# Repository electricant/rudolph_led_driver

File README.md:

# rudolph_led_driver
Driver for LED fairy lights using Li-Ion batteries

## Board pictures

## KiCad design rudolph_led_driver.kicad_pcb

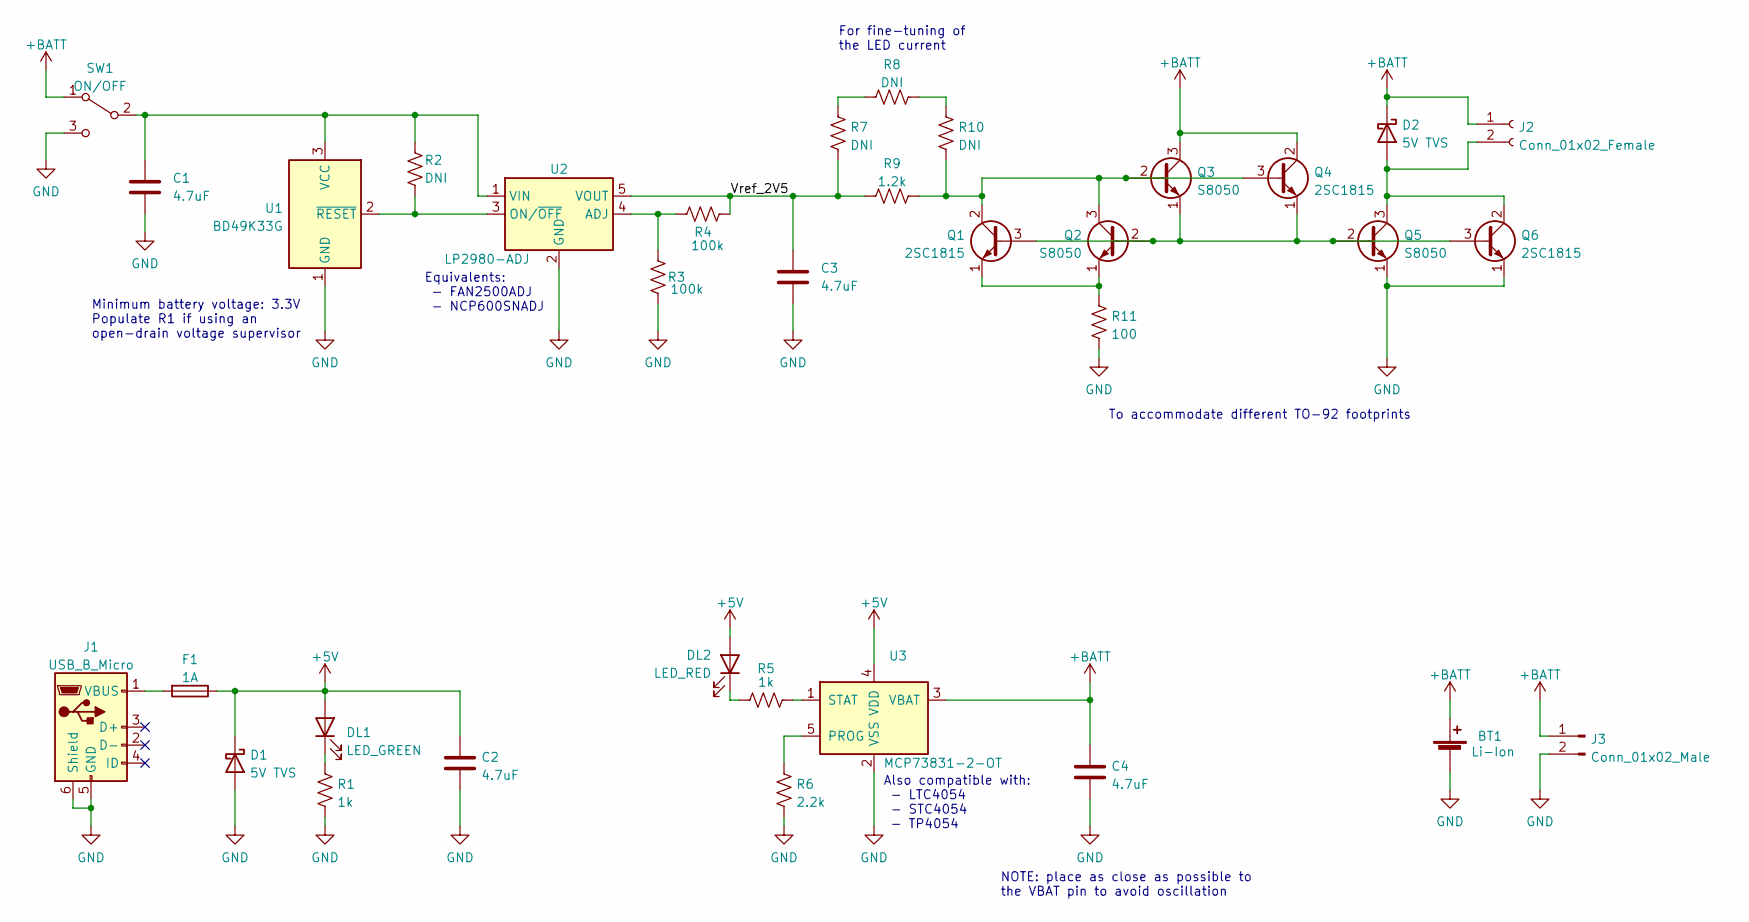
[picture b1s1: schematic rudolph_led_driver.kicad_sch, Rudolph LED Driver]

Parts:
BT1: Li-Ion; BatteryHolder_MPD_BH-18650-PC2
C1, C2, C3, C4: 4.7uF; C_0805_2012Metric_Pad1.18x1.45mm_HandSolder
D1, D2: 5V TVS; D_SOD-323_HandSoldering
DL1: LED_GREEN; D_0805_2012Metric_Pad1.15x1.40mm_HandSolder
DL2: LED_RED; D_0805_2012Metric_Pad1.15x1.40mm_HandSolder
F1: 1A; Fuse_0805_2012Metric_Pad1.15x1.40mm_HandSolder
J1: USB_B_Micro; USB_Micro-AB_Molex_47590-0001
J2: Conn_01x02_Female; PinSocket_1x02_P2.54mm_Vertical
J3: Conn_01x02_Male; PinHeader_1x02_P2.54mm_Vertical
Q1, Q4, Q6: 2SC1815; TO-92_Inline_Wide
Q2, Q3, Q5: S8050; TO-92_Inline_Wide
R1, R5: 1k; R_0805_2012Metric_Pad1.20x1.40mm_HandSolder
R2, R7, R8, R10: DNI; R_0805_2012Metric_Pad1.20x1.40mm_HandSolder
R3, R4: 100k; R_0805_2012Metric_Pad1.20x1.40mm_HandSolder
R6: 2.2k; R_0805_2012Metric_Pad1.20x1.40mm_HandSolder
R9: 1.2k; R_0805_2012Metric_Pad1.20x1.40mm_HandSolder
R11: 100; R_0805_2012Metric_Pad1.20x1.40mm_HandSolder
SW1: ON/OFF; PinHeader_1x03_P2.54mm_Vertical
U1: BD49K33G; SOT-23
U2: LP2980-ADJ; SOT-23-5
U3: MCP73831-2-OT; SOT-23-5

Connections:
+5V: C2.1, D1.1 (K), DL1.2 (A), DL2.2 (A), F1.1, U3.4 (VDD)
+BATT: BT1.1 (+), C4.1, D2.1 (K), J2.1, J3.1, Q3.3 (C), Q4.2 (C), SW1.1 (A), U3.3 (VBAT)
/Vref_2V5: C3.1, R4.2, R7.1, R9.1, U2.5 (VOUT)
GND: BT1.2 (-), C1.2, C2.2, C3.2, C4.2, D1.2 (A), J1.5 (GND), J1.6 (Shield), J3.2, Q5.1 (E), Q6.1 (E), R1.2, R3.2, R6.2, R11.2, SW1.3 (C), U1.1 (GND), U2.2 (GND), U3.2 (VSS)
unnamed: D2.2 (A), J2.2, Q5.3 (C), Q6.2 (C)
unnamed: DL1.1 (K), R1.1
unnamed: DL2.1 (K), R5.1
unnamed: F1.2, J1.1 (VBUS)
unnamed: Q1.3 (B), Q2.2 (B), Q3.1 (E), Q4.1 (E), Q5.2 (B), Q6.3 (B)
unnamed: Q1.2 (C), Q2.3 (C), Q3.2 (B), Q4.3 (B), R9.2, R10.1
unnamed: Q1.1 (E), Q2.1 (E), R11.1
unnamed: R7.2, R8.1
unnamed: R8.2, R10.2
unnamed: C1.1, R2.1, SW1.2 (B), U1.3 (VCC), U2.1 (VIN)
unnamed: R2.2, U1.2 (~RESET), U2.3 (ON/~OFF)
unnamed: R3.1, R4.1, U2.4 (ADJ)
unnamed: R6.1, U3.5 (PROG)
unnamed: R5.2, U3.1 (STAT)

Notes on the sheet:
Equivalents: - FAN2500ADJ - NCP600SNADJ
For fine-tuning of the LED current
Minimum battery voltage: 3.3V Populate R1 if using an open-drain voltage supervisor
NOTE: place as close as possible to the VBAT pin to avoid oscillation
Also compatible with: - LTC4054 - STC4054 - TP4054
To accommodate different TO-92 footprints

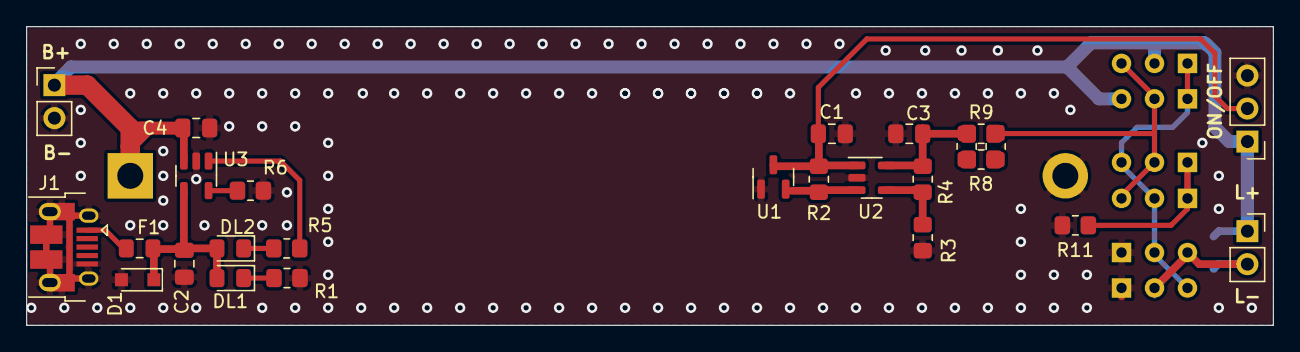
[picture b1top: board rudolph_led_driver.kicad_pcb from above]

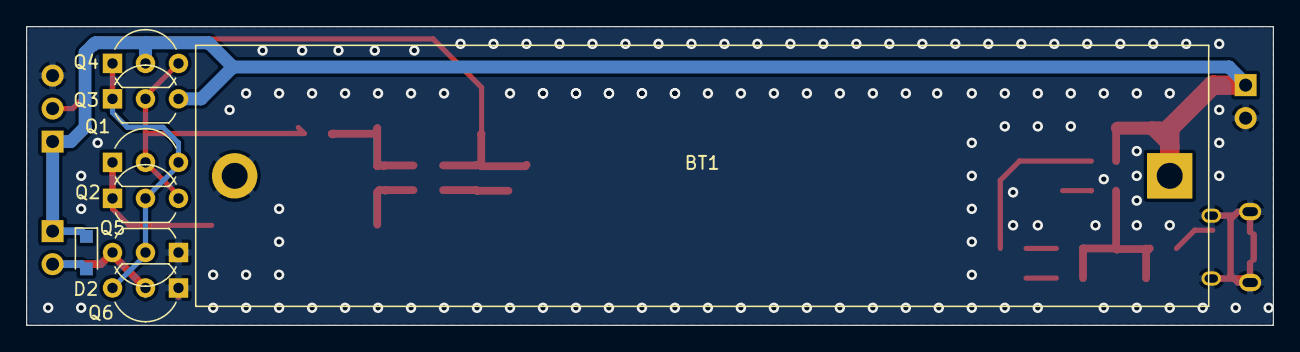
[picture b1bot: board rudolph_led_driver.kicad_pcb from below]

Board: 2 copper layers, 96.0 x 23.0 mm, 34 parts (8 on the bottom side), 18 nets.

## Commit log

2023-06-02 Add pictures of the board
2023-06-02 Update README.md with board pictures
2023-06-02 Add image of Rudolph driving LEDs
2023-10-05 Minor tweaks to the voltage reference generator
